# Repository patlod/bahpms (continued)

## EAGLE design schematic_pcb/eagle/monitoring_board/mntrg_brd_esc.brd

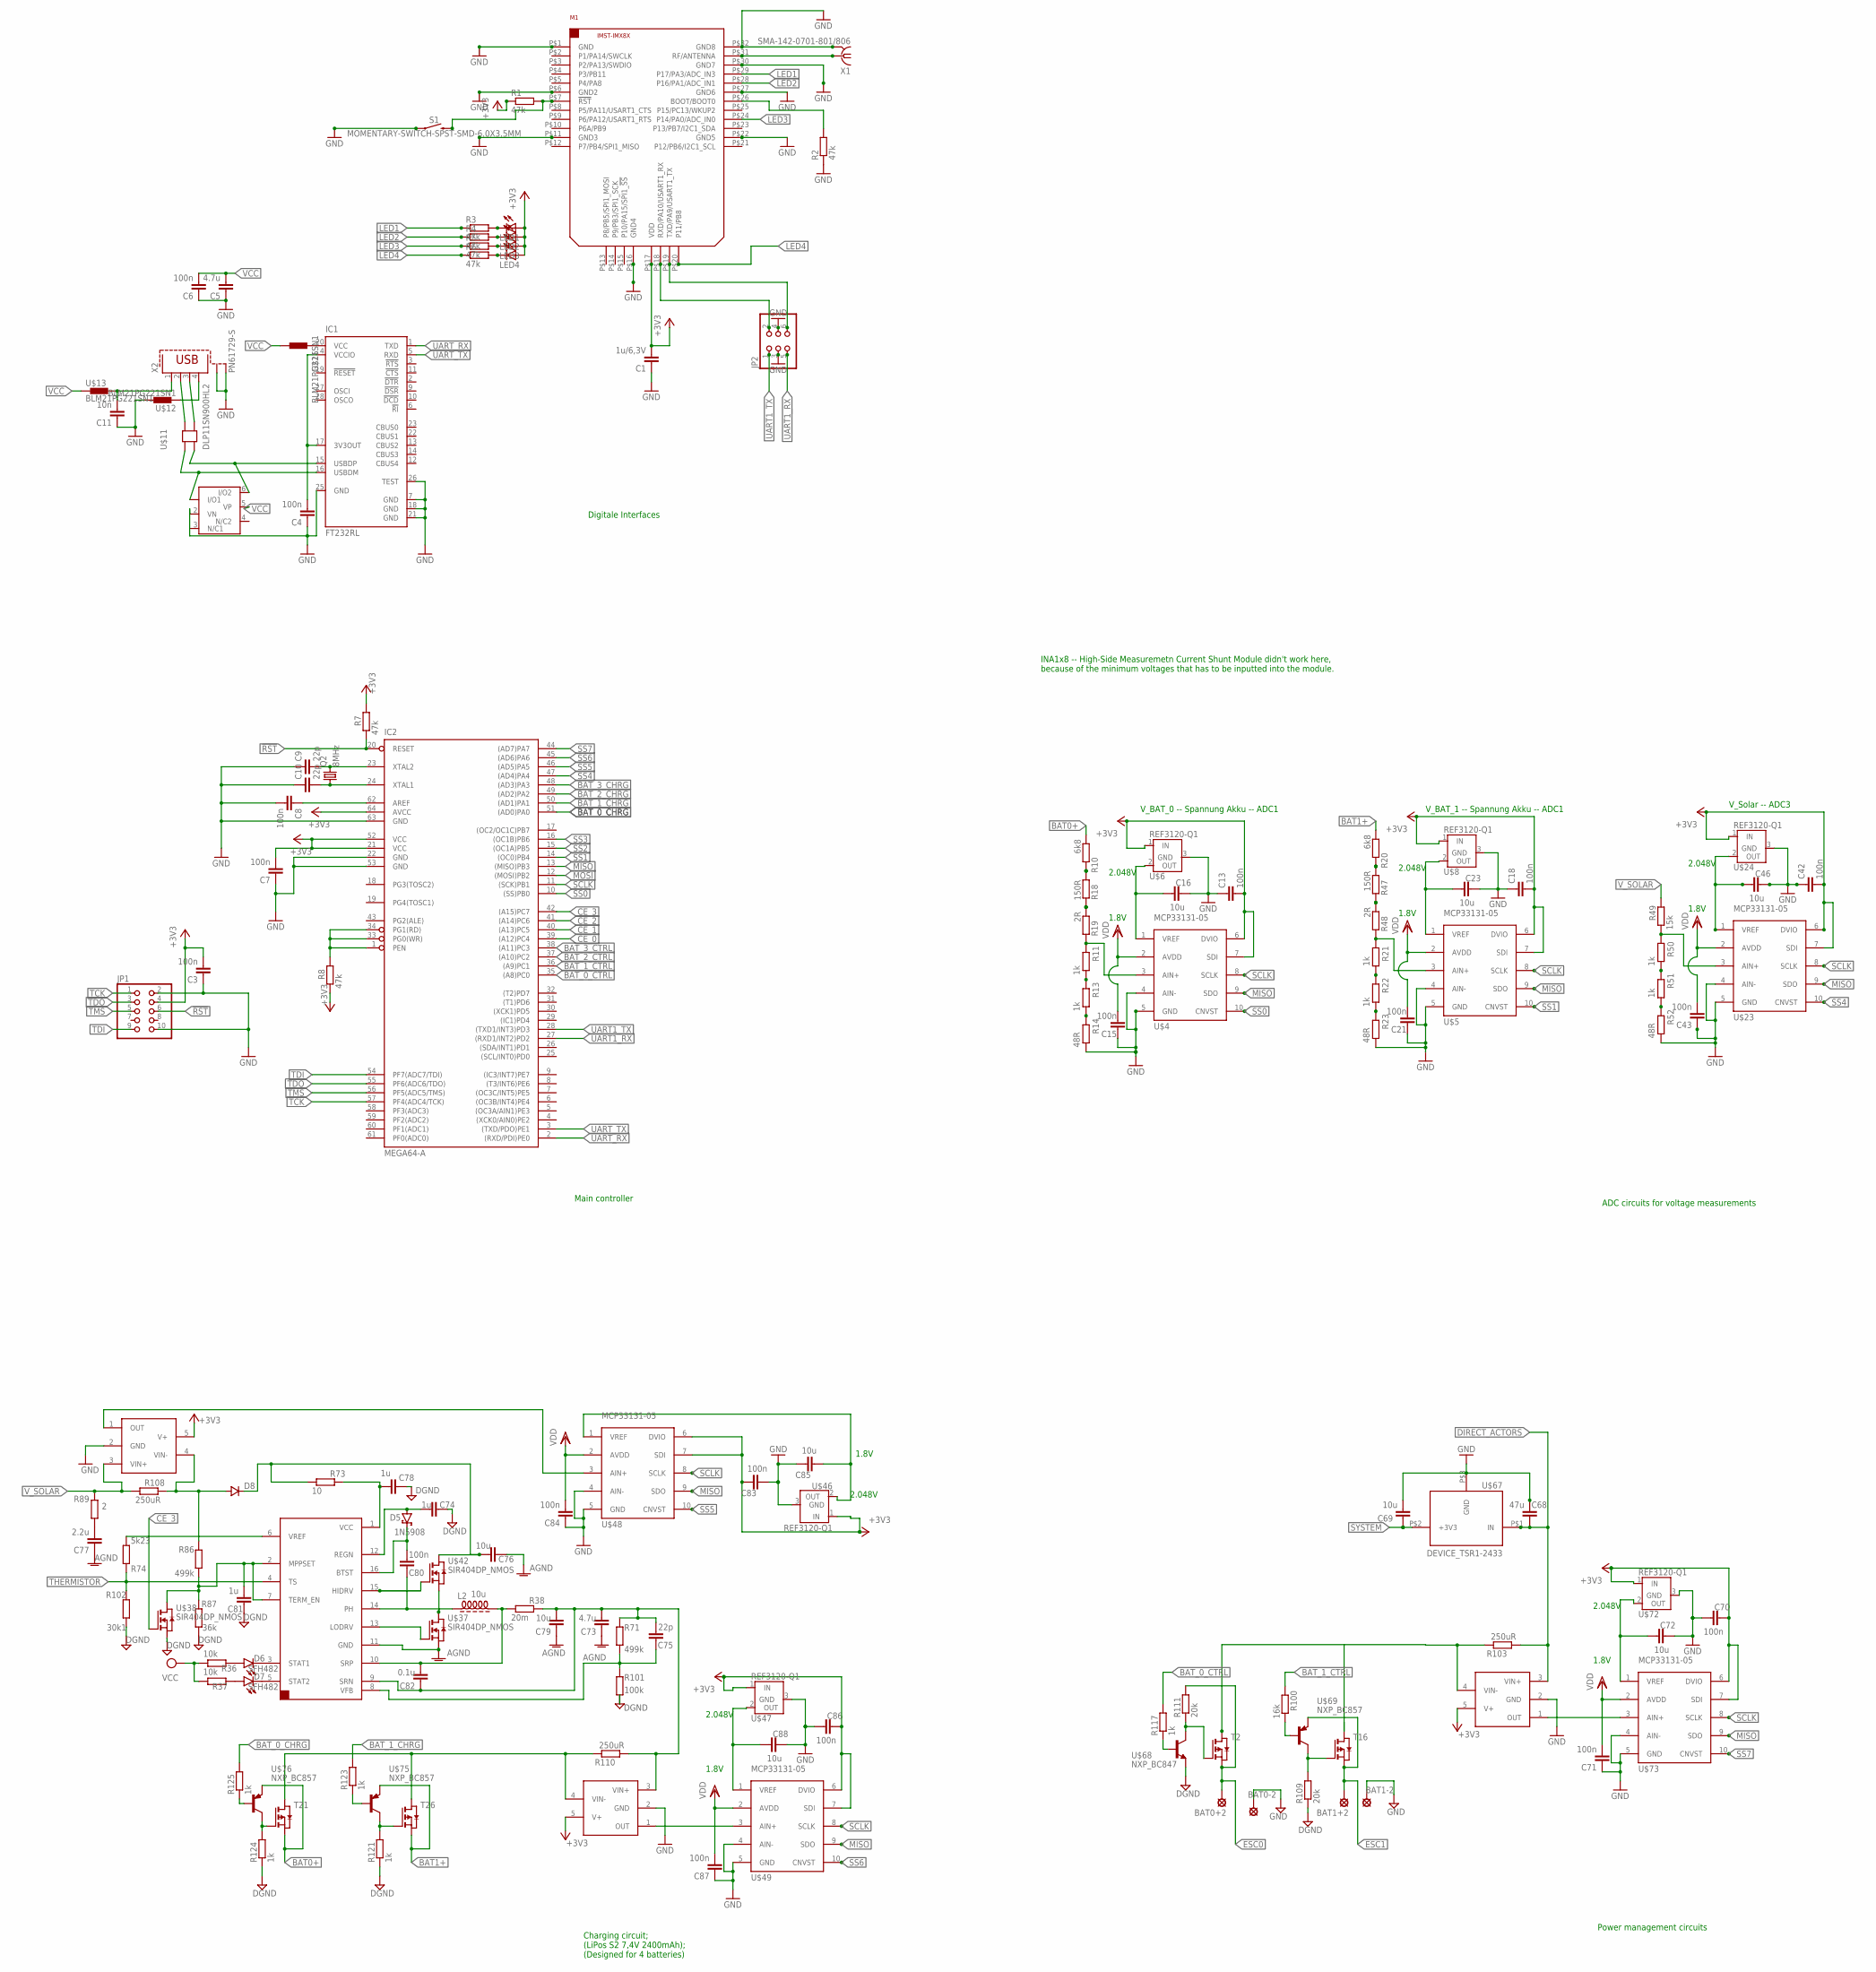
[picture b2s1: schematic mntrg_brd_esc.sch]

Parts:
BAT0+2, BAT0-2, BAT1+2, BAT1-2: SE14
C1: 1u/6,3V; C0603
C3, C4, C6, C7, C8, C13, C15, C18, C21, C42, C43, C70, C71, C80, C83, C84, C86, C87: 100n; C0603
C5, C73: 4.7u; C0603
C9, C10, C75: 22p; C0603
C11: 10n; C0603
C16, C23, C46, C72, C76, C79, C85, C88: 10u; C0603
C68: 47u; C1206
C69: 10u; C1206
C74, C78, C81: 1u; C0603
C77: 2.2u; C0603
C82: 0.1u; C0603
D5: 1N5908; C4111-15
D6, D7: SFH482
D8: VAR2SOT23; SOT-23
IC1: FT232RL; SSOP28
IC2: MEGA64-A; TQFP64
JP1: PINHD-2X5; 2X05
JP2: PINHD-2X3; 2X03
L2: 10u; Z15/1
LED1, LED2, LED3, LED4: LEDCHIP-LED0603; CHIP-LED0603
M1: IM-X8X
Q2: 8MHz; HC49/S
R1, R2, R3, R4, R5, R6, R7, R8: 47k; R0603
R10, R20: 6k8; R0603
R11, R13, R21, R22, R50, R51, R117, R121, R123, R124, R125: 1k; R0603
R14, R23, R52: 48R; R0603
R18, R47: 150R; R0603
R19, R48: 2R; R0603
R36, R37: 10k; R0603
R38: 20m; R0603
R49: 15k; R0603
R71, R86: 499k; R0603
R73: 10; R0603
R74: 5k23; R0603
R87: 36k; R0603
R89: 2; R0603
R100: 16k; R0603
R101: 100k; R0603
R102: 30k1; R0603
R103, R108, R110: 250uR; R0603
R109, R111: 20k; R0603
S1: MOMENTARY-SWITCH-SPST-SMD-6.0X3.5MM; TACTILE_SWITCH_SMD_6.0X3.5MM
T2, T16, T21, T26: SI7157DP_PMOS
U$4, U$5, U$23, U$48, U$49, U$73: MCP33131-05
U$6, U$8, U$24, U$46, U$47, U$72: REF3120-Q1
U$11: DLP11SN900HL2
U$12, U$13, U$15: BLM21PG221SN1
U$14: DUP2201MR6; NUP2201MR6
U$36: BQ24650
U$37, U$38, U$42: SIR404DP_NMOS
U$50, U$51, U$74: INA138
U$67: DEVICE_TSR1-2433; FOOTPRINT_TSR1-2344
U$68: NXP_BC847
U$69, U$75, U$76: NXP_BC857
X1: SMA-142-0701-801/806; J502-ND-142-0701-801/806
X2: PN61729-S

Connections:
!RST: IC2.20 (RESET), R7.1
+3V3: C1.2, C3.2, C7.2, C13.2, C18.2, C42.2, C70.2, C83.2, C86.2, IC2.21 (VCC), IC2.52 (VCC), IC2.64 (AVCC), JP1.4, LED1.A, LED2.A, LED3.A, LED4.A, M1.P$17 (VDD), R1.1, R7.2, R8.1, U$4.6 (DVIO), U$4.7 (SDI), U$5.6 (DVIO), U$5.7 (SDI), U$6.1 (IN), U$8.1 (IN), U$23.6 (DVIO), U$23.7 (SDI), U$24.1 (IN), U$46.1 (IN), U$47.1 (IN), U$48.6 (DVIO), U$48.7 (SDI), U$49.6 (DVIO), U$49.7 (SDI), U$50.5 (V+), U$51.5 (V+), U$72.1 (IN), U$73.6 (DVIO), U$73.7 (SDI), U$74.5 (V+)
AGND: C73.1, C76.1, C77.1, C79.1, U$36.11 (GND), U$37.1 (S), U$37.2 (S), U$37.3 (S)
BAT0+: R10.1, T21.1 (S), T21.2 (S), T21.3 (S), U$76.2 (E)
BAT1+: R20.1, T26.1 (S), T26.2 (S), T26.3 (S), U$75.2 (E)
BATTERY2: C73.2, C75.2, C79.2, C82.1, R38.2, R71.2, R110.1, U$36.9 (SRN), U$50.3 (VIN+)
BAT_0_CHRG: IC2.51 ((AD0)PA0), R125.2
BAT_0_CTRL: R117.2
BAT_1_CHRG: IC2.50 ((AD1)PA1), R123.2
BAT_1_CTRL: R100.2
BAT_2_CHRG: IC2.49 ((AD2)PA2)
BAT_3_CHRG: IC2.48 ((AD3)PA3)
CE_0: IC2.39 ((A12)PC4)
CE_1: IC2.40 ((A13)PC5)
CE_2: IC2.41 ((A14)PC6)
CE_3: U$38.4 (G)
DGND: C74.1, C78.1, C81.1, R87.1, R101.1, R102.1, R109.1, R121.1, R124.1, U$38.1 (S), U$38.2 (S), U$38.3 (S), U$68.2 (E)
DIRECT_ACTORS: C68.1, R103.1, U$67.P$1 (IN), U$74.3 (VIN+)
ESC0: BAT0+2.MP, R111.2, T2.1 (S), T2.2 (S), T2.3 (S)
ESC1: BAT1+2.MP, T16.1 (S), T16.2 (S), T16.3 (S), U$69.2 (E)
GND: BAT0-2.MP, BAT1-2.MP, C1.1, C3.1, C4.1, C5.1, C6.1, C7.1, C8.2, C9.1, C10.1, C11.1, C13.1, C15.1, C16.2, C18.1, C21.1, C23.2, C42.1, C46.2, C68.2, C69.2, C70.1, C71.1, C72.2, C83.1, C84.1, C85.2, C86.1, C87.1, C88.2, IC1.7 (GND), IC1.18 (GND), IC1.21 (GND), IC1.25 (GND), IC1.26 (TEST), IC2.22 (GND), IC2.53 (GND), IC2.63 (GND), JP1.2, JP1.10, JP2.3, JP2.4, M1.P$1 (GND), M1.P$6 (GND2), M1.P$11 (GND3), M1.P$16 (GND4), M1.P$22 (GND5), M1.P$27 (GND6), M1.P$30 (GND7), M1.P$32 (GND8), R2.1, R14.2, R23.2, S1.1, U$4.4 (AIN-), U$4.5 (GND), U$5.4 (AIN-), U$5.5 (GND), U$6.3 (GND), U$8.3 (GND), U$12.2, U$14.2 (VN), U$24.3 (GND), U$46.3 (GND), U$47.3 (GND), U$48.4 (AIN-), U$48.5 (GND), U$49.4 (AIN-), U$49.5 (GND), U$50.2 (GND), U$51.2 (GND), U$67.P$3 (GND), U$72.3 (GND), U$73.4 (AIN-), U$73.5 (GND), U$74.2 (GND), X1.G@1 (2), X1.G@2 (2), X1.G@3 (2), X1.G@4 (2), X2.S1, X2.S2
GND1: C43.1, R52.2, U$23.4 (AIN-), U$23.5 (GND)
LED1: M1.P$29 (P17/PA3/ADC_IN3), R3.1
LED2: M1.P$28 (P16/PA1/ADC_IN1), R4.1
LED3: M1.P$24 (P14/PA0/ADC_IN0), R5.1
LED4: M1.P$20 (P11/PB8), R6.1
MISO: IC2.13 ((MISO)PB3), U$4.9 (SDO), U$5.9 (SDO), U$23.9 (SDO), U$48.9 (SDO), U$49.9 (SDO), U$73.9 (SDO)
MOSI: IC2.12 ((MOSI)PB2)
unnamed: M1.P$31 (RF/ANTENNA), X1.1
unnamed: LED1.C, R3.2
unnamed: M1.P$7 (!RST), R1.2, S1.2
unnamed: M1.P$26 (BOOT/BOOT0), R2.2
unnamed: LED2.C, R4.2
unnamed: LED3.C, R5.2
unnamed: LED4.C, R6.2
unnamed: C9.2, IC2.23 (XTAL2), Q2.2
unnamed: C10.2, IC2.24 (XTAL1), Q2.1
unnamed: C8.1, IC2.62 (AREF)
unnamed: IC2.1 (PEN), IC2.33 (PG0(WR)), IC2.34 (PG1(RD)), R8.2
unnamed: U$11.2, X2.2
unnamed: U$11.4, X2.3
unnamed: IC1.16 (USBDM), U$11.1, U$14.1 (I/O1)
unnamed: IC1.15 (USBDP), U$11.3, U$14.6 (I/O2)
unnamed: U$12.1, X2.4
unnamed: C16.1, U$4.1 (VREF), U$6.2 (OUT)
unnamed: R11.1, R19.2, U$4.3 (AIN+)
unnamed: R13.2, R14.1
unnamed: C4.2, IC1.4 (VCCIO), IC1.17 (3V3OUT)
unnamed: R11.2, R13.1
unnamed: R10.2, R18.1
unnamed: C11.2, U$13.2, X2.1
unnamed: R18.2, R19.1
unnamed: C23.1, U$5.1 (VREF), U$8.2 (OUT)
unnamed: R21.1, R48.2, U$5.3 (AIN+)
unnamed: R22.2, R23.1
unnamed: R21.2, R22.1
unnamed: R20.2, R47.1
unnamed: R47.2, R48.1
unnamed: C77.2, R89.1
unnamed: R74.1, U$36.6 (VREF)
unnamed: C81.2, R86.1, R87.2, U$36.2 (MPPSET), U$36.7 (TERM_EN)
unnamed: D6.K (C), U$36.3 (STAT1)
unnamed: D7.K (C), U$36.5 (STAT2)
unnamed: D6.A, R36.2
unnamed: D7.A, R37.2
unnamed: C46.1, U$23.1 (VREF), U$24.2 (OUT)
unnamed: R49.1, R50.1, U$23.3 (AIN+)
unnamed: R51.2, R52.1
unnamed: R50.2, R51.1
unnamed: C78.2, R73.2, U$36.1 (VCC)
unnamed: C74.2, D5.A, U$36.12 (REGN)
unnamed: C80.1, L2.1, U$36.14 (PH)
unnamed: C82.2, L2.2, R38.1, U$36.10 (SRP)
unnamed: C80.2, D5.C, U$36.16 (BTST)
unnamed: U$36.15 (HIDRV), U$42.4 (G)
unnamed: C76.2, D8.1 (C), R73.1, U$42.5 (D), U$42.6 (D), U$42.7 (D), U$42.8 (D)
unnamed: C75.1, R71.1, R101.2, U$36.8 (VFB)
unnamed: C72.1, U$72.2 (OUT), U$73.1 (VREF)
unnamed: U$73.3 (AIN+), U$74.1 (OUT)
unnamed: R103.2, T2.5 (D), T2.6 (D), T2.7 (D), T2.8 (D), T16.5 (D), T16.6 (D), T16.7 (D), T16.8 (D), U$74.4 (VIN-)
unnamed: R111.1, T2.4 (G), U$68.3 (C)
unnamed: R117.1, U$68.1 (B)
unnamed: R109.2, T16.4 (G), U$69.3 (C)
unnamed: D8.3 (A), R86.2, R108.2, U$51.4 (VIN-)
unnamed: U$38.5 (D), U$38.6 (D), U$38.7 (D), U$38.8 (D)
unnamed: U$37.5 (D), U$37.6 (D), U$37.7 (D), U$37.8 (D), U$42.1 (S), U$42.2 (S), U$42.3 (S)
unnamed: R100.1, U$69.1 (B)
unnamed: C88.1, U$47.2 (OUT), U$49.1 (VREF)
unnamed: R110.2, T21.5 (D), T21.6 (D), T21.7 (D), T21.8 (D), T26.5 (D), T26.6 (D), T26.7 (D), T26.8 (D), U$50.4 (VIN-)
unnamed: U$49.3 (AIN+), U$50.1 (OUT)
unnamed: C85.1, U$46.2 (OUT), U$48.1 (VREF)
unnamed: U$48.3 (AIN+), U$51.1 (OUT)
unnamed: R124.2, T21.4 (G), U$76.3 (C)
unnamed: R125.1, U$76.1 (B)
unnamed: R121.2, T26.4 (G), U$75.3 (C)
unnamed: R123.1, U$75.1 (B)
SCLK: IC2.11 ((SCK)PB1), U$4.8 (SCLK), U$5.8 (SCLK), U$23.8 (SCLK), U$48.8 (SCLK), U$49.8 (SCLK), U$73.8 (SCLK)
SS0: IC2.10 ((SS)PB0), U$4.10 (CNVST)
SS1: IC2.14 ((OC0)PB4), U$5.10 (CNVST)
SS2: IC2.15 ((OC1A)PB5)
SS3: IC2.16 ((OC1B)PB6)
SS4: IC2.47 ((AD4)PA4), U$23.10 (CNVST)
SS5: IC2.46 ((AD5)PA5), U$48.10 (CNVST)
SS6: IC2.45 ((AD6)PA6), U$49.10 (CNVST)
SS7: IC2.44 ((AD7)PA7), U$73.10 (CNVST)
SYSTEM: C69.1, U$67.P$2 (+3V3)
TCK: JP1.1
TDI: JP1.9
TDO: JP1.3
THERMISTOR: R74.2, R102.2, U$36.4 (TS)
TMS: JP1.5
UART1_RX: IC2.27 ((RXD1/INT2)PD2), JP2.5, JP2.6, M1.P$19 (TXD/PA9/USART1_TX)
UART1_TX: IC2.28 ((TXD1/INT3)PD3), JP2.1, JP2.2, M1.P$18 (RXD/PA10/USART1_RX)
UART_RX: IC1.1 (TXD), IC2.2 ((RXD/PDI)PE0)
UART_TX: IC1.5 (RXD), IC2.3 ((TXD/PDO)PE1)
VCC: C5.2, C6.2, IC1.20 (VCC), R36.1, R37.1, U$13.1, U$14.5 (VP), U$15.1, U$15.2
VDD: C15.2, C21.2, C43.2, C71.2, C84.2, C87.2, U$4.2 (AVDD), U$5.2 (AVDD), U$23.2 (AVDD), U$48.2 (AVDD), U$49.2 (AVDD), U$73.2 (AVDD)
V_SOLAR: R49.2, R89.2, R108.1, U$51.3 (VIN+)

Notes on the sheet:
ADC circuits for voltage measurements
Main controller
Digitale Interfaces
INA1x8 -- High-Side Measuremetn Current Shunt Module didn't work here, because of the minimum voltages that has to be inputted into the module.
Charging circuit; (LiPos S2 7,4V 2400mAh); (Designed for 4 batteries)
Power management circuits
1.8V
2.048V
V_BAT_0 -- Spannung Akku -- ADC1
V_BAT_1 -- Spannung Akku -- ADC1
V_Solar -- ADC3

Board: 2 copper layers, 141 parts (0 on the bottom side), 103 nets, no tracks yet.

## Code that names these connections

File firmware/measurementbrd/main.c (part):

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// 			  the indices of the controller pins.
// Index-translations:
// Ctrl:   FW   |   HW 		  ||	Chrg: 	FW	 |   HW
//          0	|	PA3       ||			 0   |   PA7
// 			1   |   PA0       ||			 1   |   PA4
// 			2   |   PA2       || 			 2   |   PA6
// 			3   |	PA1       ||			 3   |   PA5

#define BAT_0_CTRL 					PA3		// Default: Conducting
#define BAT_1_CTRL					PA0		// Default: Non-Conducting
#define BAT_2_CTRL  				PA2		// Default: Non-Conducting		
#define BAT_3_CTRL  				PA1		// Default: Non-Conducting

#define BAT_0_CHRG  				PA7		// Default: Non-Conducting
#define BAT_1_CHRG  				PA4		// Default: Non-Conducting
#define BAT_2_CHRG  				PA6		// Default: Non-Conducting
#define BAT_3_CHRG  				PA5		// Default: Non-Conducting

/* ------- Management mode -------- */
#define NUM_2_BAT						2
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#define BAT_MAX_VOLTS				16.8 - 0.05
#endif

/* ------- Constants for "Rest" times in 3-Bat system ------- */
// Simple strategy:
// As the voltage of lithium-ion batteries has a plateau somewhere between
// 80% (and 20%) we just use exactly these limits to start charging.
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 * Initializes output pins used in the management routines. 
 */
void ctrl_pin_init(void) {
	// Set pins PA0...PA7 as OUTPUT in GPIO Register A
	DDRA |=  ( (1 << PA7) | (1 << PA6) | (1 << PA5) | (1 << PA4)  | (1 << PA3) | (1 << PA2) | (1 << PA1) | (1 << PA0) );
	// Set all pins to zero in PORTA
	PORTA &= ~ ( (1 << PA7) | (1 << PA6) | (1 << PA5) | (1 << PA4)  | (1 << PA3) | (1 << PA2) | (1 << PA1) | (1 << PA0) );
}


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
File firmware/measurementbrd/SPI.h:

/*
 * SPI.h
 *
 * Created: 11.11.2019 12:42:03
 *  Author: patrickl
 */ 


#ifndef SPI_H_
#define SPI_H_
#include <avr/io.h>

/************************************************************************/
/* Mapping SPI pins ADC MCP33131-05 onto pins ATmega64                  */
/* ATmega64         ADC													*/
/* --------		   ------											*/
/* PB0 (~SS0)      CNVST0												*/
/* PB1 (SCK)        SCLK												*/
/* PB2 (MOSI)		none												*/
/* PB3 (MISO)     SDO_{0..3}											*/
/* PC7 (~SS1)      CNVST1												*/
/*   ...												*/
/* PC1 (~SS7)      CNVST7												*/
/************************************************************************/


/* Slave select lines for the external ADCs */

#define DD_SCK		PB1
#define DD_MOSI		PB2
#define DD_MISO		PB3
#define DD_SS0		PB0		// V_BAT_0+

#define DD_SS1		PC7		// V_BAT_1+
#define DD_SS2		PC6		// V_BAT_2+
#define DD_SS3		PC5		// V_BAT_3+
#define DD_SS4		PC4		// V_SOLAR+
#define DD_SS5		PC3		// I_SOLAR
#define DD_SS6		PC2		// I_CHARGE
#define DD_SS7		PC1		// I_LOAD



void spi_init();
void spi_tx(uint8_t slave);



#endif /* SPI_H_ */

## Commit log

2020-07-12 Created repository
2021-03-16 Added images
2021-03-16 Images links in README.md
2021-03-16 file extensions links
2021-03-16 image links
2021-03-16 .gitignore
